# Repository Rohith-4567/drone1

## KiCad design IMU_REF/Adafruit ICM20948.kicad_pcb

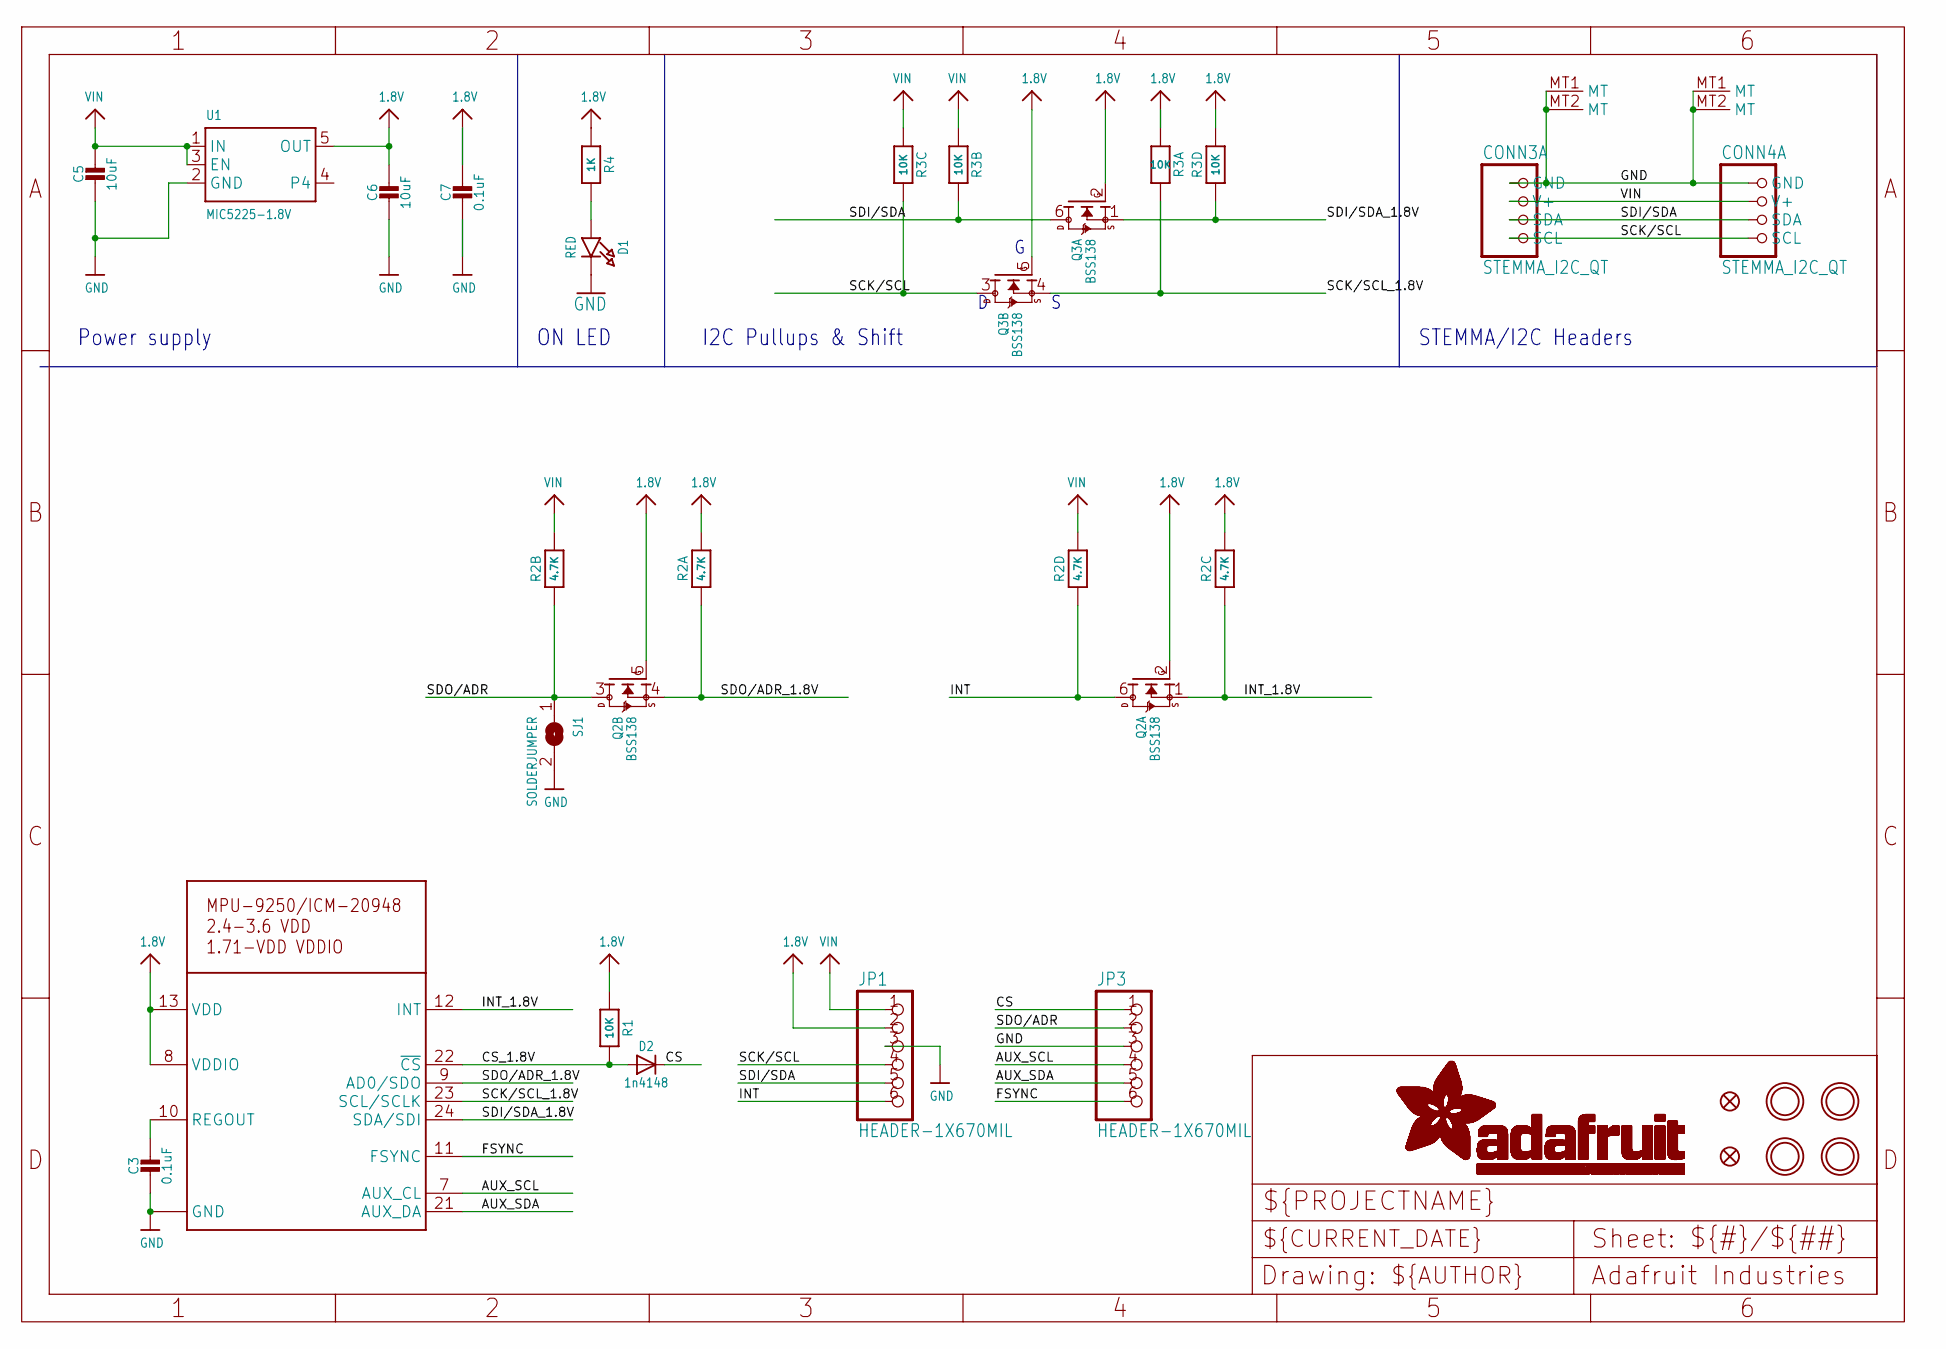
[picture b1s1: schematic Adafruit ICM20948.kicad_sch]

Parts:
C3, C7: 0.1uF; 0603-NO
C5, C6: 10uF; 0805-NO
CONN3, CONN4: STEMMA_I2C_QT; JST_SH4
D1: RED; CHIPLED_0603_NOOUTLINE
D2: 1n4148; SOD-323_MINI
FID2, FID4: FIDUCIAL_1MM
JP1, JP3: HEADER-1X670MIL; 1X06_ROUND_70
Q2, Q3: BSS138; SOT363
R1: 10K; 0603-NO
R2: 4.7K; RESPACK_4X0603
R3: 10K; RESPACK_4X0603
R4: 1K; 0603-NO
SJ1: SOLDERJUMPER; SOLDERJUMPER_ARROW_NOPASTE
U1: MIC5225-1.8V; SOT23-5
U$21: MPU-9250_ICM20948; QFN24_3MM_NOEP
U$38, U$39, U$41, U$42: MOUNTINGHOLE2.5; MOUNTINGHOLE_2.5_PLATED

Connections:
1.8V: C6.1, C7.1, JP1.2, Q2.2 (G), Q2.5 (G), Q3.2 (G), Q3.5 (G), R1.1, R2.6 (2), R2.8 (2), R3.4 (1), R3.8 (2), R4.1, U1.5 (OUT), U$21.8 (VDDIO), U$21.13 (VDD)
AUX_SCL: JP3.4, U$21.7 (AUX_CL)
AUX_SDA: JP3.5, U$21.21 (AUX_DA)
CS: D2.C, JP3.1
CS_1.8V: D2.A, R1.2, U$21.22 (~CS)
FSYNC: JP3.6, U$21.11 (FSYNC)
GND: C3.2, C5.2, C6.2, C7.2, CONN3.1 (GND), CONN3.MT1 (MT), CONN3.MT2 (MT), CONN4.1 (GND), CONN4.MT1 (MT), CONN4.MT2 (MT), D1.C, JP1.3, JP3.3, SJ1.2, U1.2 (GND), U$21.18 (GND), U$21.20 (GND)
INT: JP1.6, Q2.6 (D), R2.4 (1)
INT_1.8V: Q2.1 (S), R2.3 (1), U$21.12 (INT)
unnamed: D1.A, R4.2
REGOUT: C3.1, U$21.10 (REGOUT)
SCK/SCL: CONN3.4 (SCL), CONN4.4 (SCL), JP1.4, Q3.3 (D), R3.6 (2)
SCK/SCL_1.8V: Q3.4 (S), R3.1, U$21.23 (SCL/SCLK)
SDI/SDA: CONN3.3 (SDA), CONN4.3 (SDA), JP1.5, Q3.6 (D), R3.7 (2)
SDI/SDA_1.8V: Q3.1 (S), R3.5 (2), U$21.24 (SDA/SDI)
SDO/ADR: JP3.2, Q2.3 (D), R2.2 (1), SJ1.1
SDO/ADR_1.8V: Q2.4 (S), R2.1, U$21.9 (AD0/SDO)
VIN: C5.1, CONN3.2 (V+), CONN4.2 (V+), JP1.1, R2.5 (2), R2.7 (2), R3.2 (1), R3.3 (1), U1.1 (IN), U1.3 (EN)

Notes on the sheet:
ON LED
Power supply
STEMMA/I2C Headers
I2C Pullups & Shift

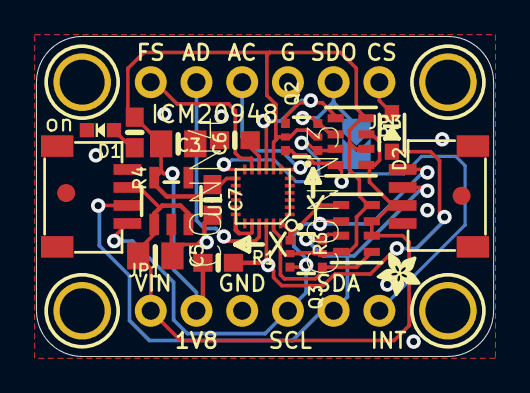
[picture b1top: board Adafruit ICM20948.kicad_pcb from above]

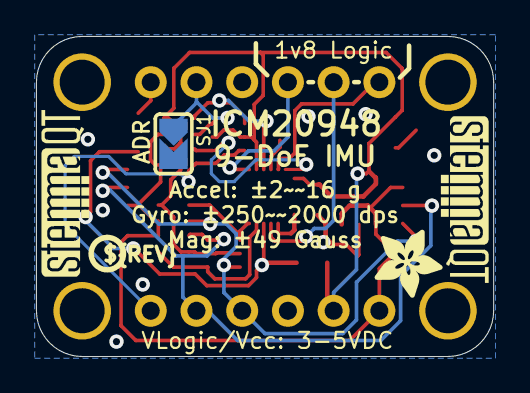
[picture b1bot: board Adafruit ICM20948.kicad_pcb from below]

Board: 2 copper layers, 25.4 x 17.8 mm, 30 parts (5 on the bottom side), 18 nets.

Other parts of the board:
U$2: ADAFRUIT_2.5MM
U$12: ADAFRUIT_3.5MM
U$45: PCBFEAT-REV-040
U$46, U$47: STEMMAQT

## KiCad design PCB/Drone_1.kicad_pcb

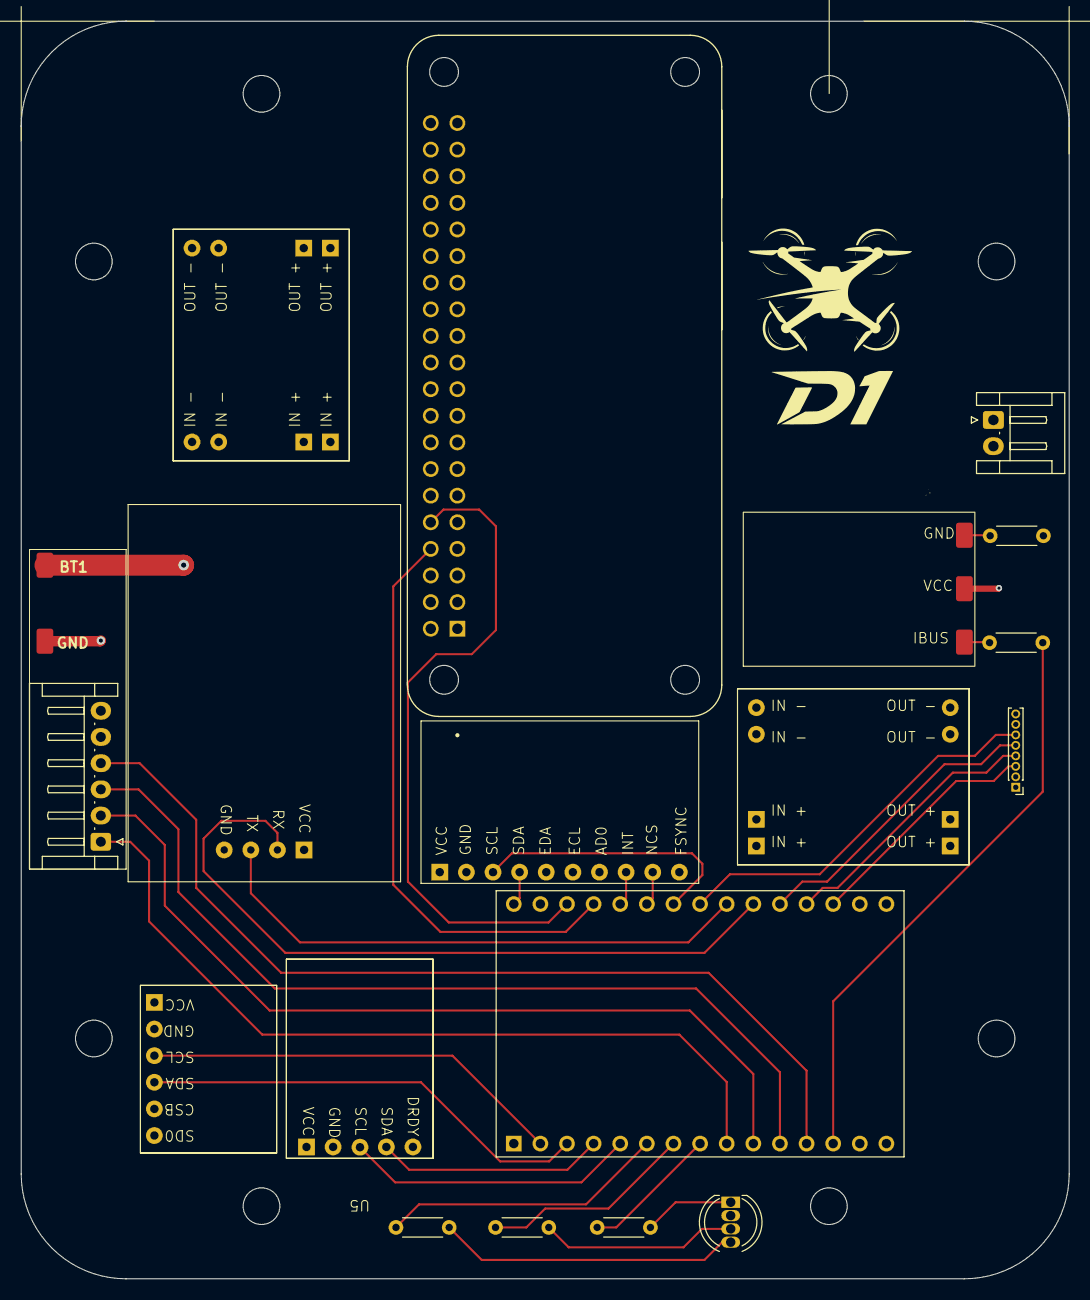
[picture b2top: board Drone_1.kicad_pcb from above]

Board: 4 copper layers, 100.0 x 120.0 mm, 26 parts (0 on the bottom side), 33 nets.

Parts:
BT1: Battery; JST_EH_S2B-EH_1x02_P2.50mm_Horizontal
D1: APA-106-F5; LED_D5.0mm-4_RGB
H1, H2, H3, H4, H5, H6, H7, H8: MountingHole; MountingHole_3.5mm
J1: ESP-32_DevkitC; ESP32-C3-DevKitM-1
J2: Conn_01x08_Pin; PinHeader_1x08_P1.00mm_Vertical
R1, R2, R3: 220; R_Axial_DIN0204_L3.6mm_D1.6mm_P5.08mm_Horizontal
R4: 3.3K; R_Axial_DIN0204_L3.6mm_D1.6mm_P5.08mm_Horizontal
R5: 2K; R_Axial_DIN0204_L3.6mm_D1.6mm_P5.08mm_Horizontal
U1: Rasberry Pi 0W; MODULE_SC0065
U3: GY-NEO6MV2; GY-NEO6MV2foot
U4: BME280; BME280_footprint
U5: HMC5883L; HMC5883L_footprint
U6, U7: mp1584; mp1584_footprint
U8: Flysky fs-a8s; Flysky fs-a8s_footprint
U9: MPU6500
U10: 4x1_ESC

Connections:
0: BT1.2 (-), D1.2 (GND), J1.14, J2.1, J2.8, R5.1, U1.6 (GND_6), U3.4 (GND), U4.2 (GND), U5.2 (GND), U6.4 (OUT-), U6.5 (IN-), U7.4 (OUT-), U7.5 (IN-), U9.2 (GND), U10.1 (GND), U10.13 (GND)
+3.3V: J1.15, J2.2, U3.1 (VCC), U4.1 (VCC), U4.5 (CSB), U5.1 (VCC), U6.1 (OUT+), U9.1 (VCC)
+5V: J2.7, U1.2 (5V_2), U7.1 (OUT+), U8.2 (VCC)
+7.5V: BT1.1 (+), U6.8 (IN+), U7.8 (IN+), U10.14 (BT1)
unnamed: D1.4 (DI), R3.1
unnamed: D1.1 (DO), R1.1
unnamed: D1.3 (VDD), R2.1
unnamed: J1.2, U4.3 (SCL)
unnamed: J1.3, U4.4 (SDA)
unnamed: J1.4, U5.4 (SDA)
unnamed: J1.5, U5.3 (SCL)
unnamed: J1.6, R3.2
unnamed: J1.7, R2.2
unnamed: J1.8, R1.2
unnamed: J1.9, U10.6 (PWM4)
unnamed: J1.10, U10.5 (PWM3)
unnamed: J1.11, U10.4 (PWM2)
unnamed: J1.12, U10.3 (PWM1)
unnamed: J1.13, R4.1
unnamed: J1.18, J2.3
unnamed: J1.19, J2.4
unnamed: J1.20, J2.5
unnamed: J1.21, U3.2 (RX)
unnamed: J1.22, U3.3 (TX)
unnamed: J1.23, J2.6
unnamed: J1.24, U9.3 (SCL)
unnamed: J1.25, U9.9 (NCS)
unnamed: J1.26, U9.8 (INT)
unnamed: J1.27, U1.8 (GPIO14/TXD0)
unnamed: J1.28, U1.10 (GPIO15/RXD0)
unnamed: J1.30, U9.4 (SDA)
unnamed: R5.2, U8.1 (GND)
unnamed: R4.2, U8.3 (SBUS)

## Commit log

2025-07-14 welcome
2025-08-05 fixed code for motors
2025-08-08 added motor code
2025-08-08 added ESC folder and MPU folder code
2025-08-08 added python simulation
2025-08-09 added multithreading to web accesspoint and made platformio compatible
2025-08-11 added PID
2025-08-11 most up to date
2025-08-16 added pitch drone control
2026-01-30 Super Loop code (V1), flight extremely unstable
2026-01-30 added freertos code
2026-01-30 most recent changes from AnshuDrive:
2026-05-19 added mini drone files
2026-05-19 added chassis files
2026-05-30 esp mini drone schematic
